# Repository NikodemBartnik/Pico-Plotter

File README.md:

# Pico Plotter

3D printed Raspberry Pi Pico H-Bot plotter programmed in MicroPython capable of drawing on paper and burning wood with versatip.

## Description

Main purpose of this project was to practice Python programing, design something cool and understand basics of how CNC machines, Gcode senders etc. works. This project is probably a great starting point to learn about basics of any CNC machine, as it is very simple and code is very minimal. 3D printed parts are optimized for support less printing (most of them but not all) and can be printed out of PLA. 
## Parts
#### Electronics
| Name                  | Amount | Link 1                                           | Link 2                                           | Link 3                                             |
| --------------------- | ------ | ------------------------------------------------ | ------------------------------------------------ | -------------------------------------------------- |
| Motors                | 2      | [https://bit.ly/3jrCJqY](https://bit.ly/3jrCJqY) | [https://bit.ly/3w9vsim](https://bit.ly/3w9vsim) | [https://amzn.to/3jlCU7o](https://amzn.to/3jlCU7o) |
| Stepper drivers       | 2      | [https://bit.ly/3608XSl](https://bit.ly/3608XSl) | [https://bit.ly/3Abaz9P](https://bit.ly/3Abaz9P) | [https://amzn.to/3yjyXV9](https://amzn.to/3yjyXV9) |
| Power supply          | 1      | [https://bit.ly/3qzeEjz](https://bit.ly/3qzeEjz) | [https://bit.ly/3qzJbxF](https://bit.ly/3qzJbxF) | [https://amzn.to/2T9NVOx](https://amzn.to/2T9NVOx) |
| Raspberry Pi Pico     | 1      | [https://bit.ly/2US6Spl](https://bit.ly/2US6Spl) | [https://bit.ly/3Aegafp](https://bit.ly/3Aegafp) | [https://amzn.to/2Tjz9Vd](https://amzn.to/2Tjz9Vd) |
| USB to UART converter | 1      | [https://bit.ly/3vZQIqF](https://bit.ly/3vZQIqF) | [https://bit.ly/36488Il](https://bit.ly/36488Il) | [https://amzn.to/3dsafcT](https://amzn.to/3dsafcT) |
| Micro servo           | 1      | [https://bit.ly/3A8MjoF](https://bit.ly/3A8MjoF) | [https://bit.ly/3jrOihS](https://bit.ly/3jrOihS) | [https://amzn.to/367zPQh](https://amzn.to/367zPQh) |
| Small components      | \-     |                                                  |                                                  |
#### Mechanics
| Name                         | Amount | Link 1                                           | Link 2                                           | Link 3                                             |
| ---------------------------- | ------ | ------------------------------------------------ | ------------------------------------------------ | -------------------------------------------------- |
| Aluminium profile 2020 600mm | 5      | [https://bit.ly/2UF2auT](https://bit.ly/2UF2auT) | [https://bit.ly/3hjPS2F](https://bit.ly/3hjPS2F) | [https://amzn.to/2UcRjs5](https://amzn.to/2UcRjs5) |
| MGN12 Linear rail 500mm      | 3      | [https://bit.ly/3qwWoHM](https://bit.ly/3qwWoHM) | [https://bit.ly/3jvdd4f](https://bit.ly/3jvdd4f) | [https://amzn.to/3Adcs5K](https://amzn.to/3Adcs5K) |
| MGN12H linear block          | 5      | [https://bit.ly/3qyKxsE](https://bit.ly/3qyKxsE) | [https://bit.ly/3AkVN0r](https://bit.ly/3AkVN0r) | [https://amzn.to/3h266yv](https://amzn.to/3h266yv) |
| GT2 Pulley                   | 2      | [https://bit.ly/3y7doGW](https://bit.ly/3y7doGW) | [https://bit.ly/3AbJDXp](https://bit.ly/3AbJDXp) | [https://amzn.to/3h2xc8I](https://amzn.to/3h2xc8I) |
| GT2 Belt                     | 5m     | [https://bit.ly/3h44CUH](https://bit.ly/3h44CUH) | [https://bit.ly/2U5sbDr](https://bit.ly/2U5sbDr) | [https://amzn.to/3x8Wgk0](https://amzn.to/3x8Wgk0) |
| 625ZZ Bearing                | 6      | [https://bit.ly/2USf3Sz](https://bit.ly/2USf3Sz) | [https://bit.ly/2TbLKKo](https://bit.ly/2TbLKKo) | [https://amzn.to/3vZVZyt](https://amzn.to/3vZVZyt) |
| Corner connectors            | 4      | [https://bit.ly/3h1PA1G](https://bit.ly/3h1PA1G) | [https://bit.ly/3qLDTj3](https://bit.ly/3qLDTj3) | [https://amzn.to/2Ua83Af](https://amzn.to/2Ua83Af) |
| Screws, T nuts etc.          |        |                                                  |                                                  |
#### Tools
| Name               | Link 1                                                         | Link 2                                                             | Link 3                                             |
| ------------------ | -------------------------------------------------------------- | ------------------------------------------------------------------ | -------------------------------------------------- |
| 3D printer         | [https://bit.ly/3qxoAu7](https://bit.ly/3qxoAu7)               | [https://bit.ly/3xZZaHU](https://bit.ly/3xZZaHU)                   | [https://amzn.to/3y25gHV](https://amzn.to/3y25gHV) |
| CNC Machine        | [https://indystry.cc/indymill/](https://indystry.cc/indymill/) | [https://indystry.cc/dremel-cnc/](https://indystry.cc/dremel-cnc/) |                                                    |
| Gas soldering iron | [https://amzn.to/3jEaGoH](https://amzn.to/3jEaGoH)             | [https://bit.ly/3dqgHBm](https://bit.ly/3dqgHBm)                   |
## Getting Started
You don't need any special libraries or additional files, assuming you have Python installed you have everything you need.
In order to upload script to Raspberry Pi Pico I used [Thonny](https://thonny.org/)

### Executing program
Before executing the Gcode sender change port of your raspberry pi pico and also path to the file that you want to print
To execute Gcode sender script simply change directory to where the file is located and type in the terminal:
```
python GcodeSender.py
```

## Help

If you need help, see the problem or want to contribute open an issue.

## Author
[Nikodem Bartnik](https://nikodembartnik.pl/)

## License

This project is licensed under the MIT license.

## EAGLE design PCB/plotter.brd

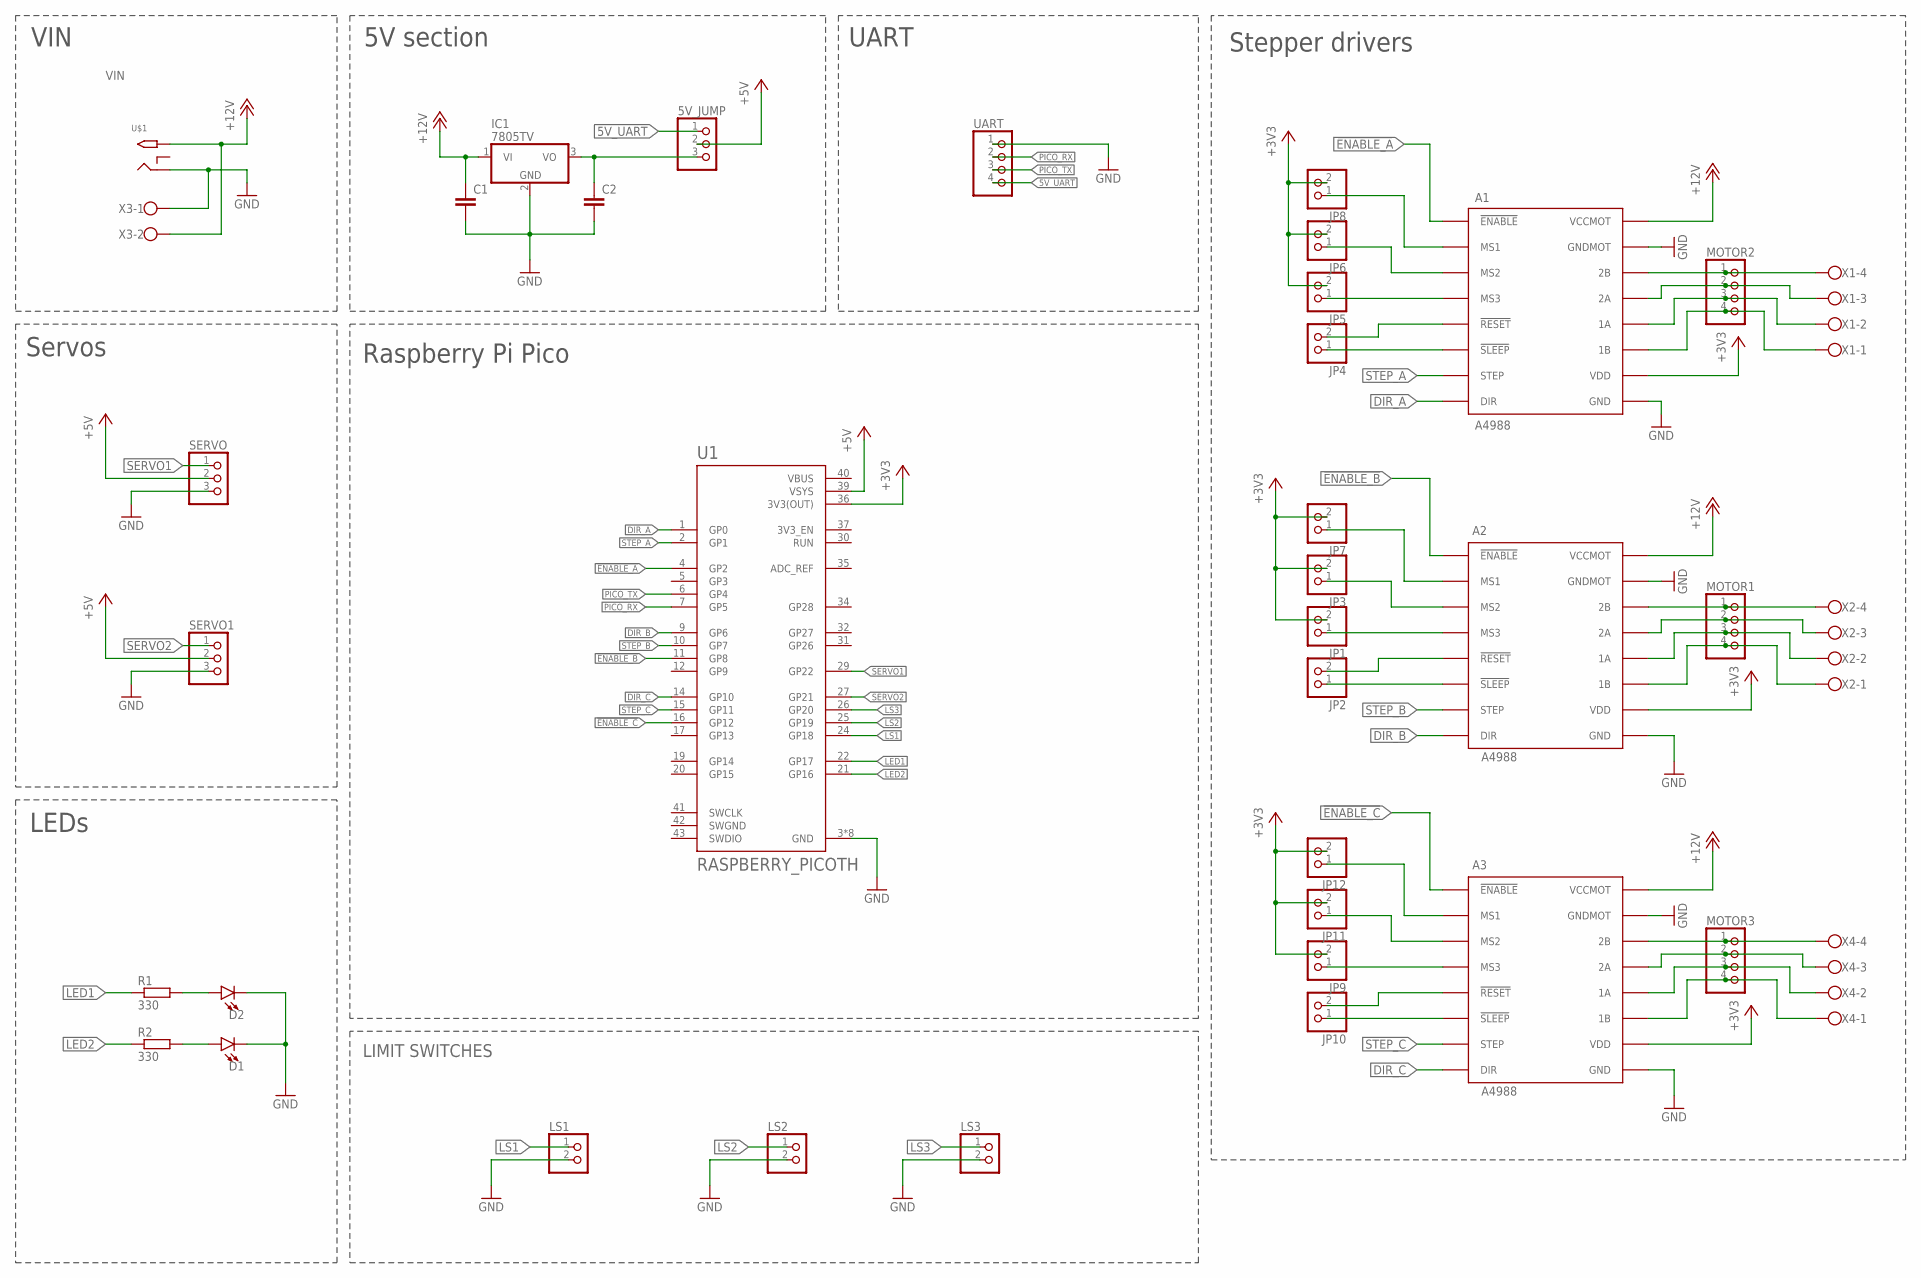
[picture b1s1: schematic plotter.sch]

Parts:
5V_JUMP: PINHD-1X3; 1X03
A1, A2, A3: A4988
C1, C2: C-EUC0805; C0805
D1, D2: LED5MM; LED_5MM
IC1: 7805TV; TO220V
JP1, JP2, JP3, JP4, JP5, JP6, JP7, JP8, JP9, JP10, JP11, JP12: PINHD-1X2; 1X02
LS1, LS2, LS3: PINHD-1X2; 1X02
MOTOR1, MOTOR2, MOTOR3: PINHD-1X4; 1X04
R1, R2: 330; R0805
SERVO, SERVO1: PINHD-1X3; 1X03
U1: RASPBERRY_PICOTH; PICO-PKG-TH
U$1: 2.1MMJACKTHM; PJ-102A
UART: PINHD-1X4; 1X04
X1, X2, X4: W237-4
X3: W237-102

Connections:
5V_UART: 5V_JUMP.1, UART.4
!ENABLE_A: A1.!ENABLE, U1.4 (GP2)
!ENABLE_B: A2.!ENABLE, U1.11 (GP8)
!ENABLE_C: A3.!ENABLE, U1.16 (GP12)
+3V3: A1.VDD, A2.VDD, A3.VDD, JP1.2, JP3.2, JP5.2, JP6.2, JP7.2, JP8.2, JP9.2, JP11.2, JP12.2, U1.36 (3V3(OUT))
+5V: 5V_JUMP.2, SERVO.2, SERVO1.2, U1.39 (VSYS)
+12V: A1.VCCMOT, A2.VCCMOT, A3.VCCMOT, C1.1, IC1.1 (VI), U$1.TIP, X3.2
DIR_A: A1.DIR, U1.1 (GP0)
DIR_B: A2.DIR, U1.9 (GP6)
DIR_C: A3.DIR, U1.14 (GP10)
GND: A1.GND, A1.GNDMOT, A2.GND, A2.GNDMOT, A3.GND, A3.GNDMOT, C1.2, C2.2, D1.K (C), D2.K (C), IC1.2 (GND), LS1.2, LS2.2, LS3.2, SERVO.3, SERVO1.3, U1.3 (GND), U1.8 (GND), U1.13 (GND), U1.18 (GND), U1.23 (GND), U1.28 (GND), U1.33 (GND), U1.38 (GND), U$1.RING, UART.1, X3.1
LED1: R1.1, U1.22 (GP17)
LED2: R2.1, U1.21 (GP16)
LS1: LS1.1, U1.24 (GP18)
LS2: LS2.1, U1.25 (GP19)
LS3: LS3.1, U1.26 (GP20)
unnamed: A1.2B, MOTOR2.1, X1.4
unnamed: A1.2A, MOTOR2.2, X1.3
unnamed: A1.1A, MOTOR2.3, X1.2
unnamed: A1.1B, MOTOR2.4, X1.1
unnamed: A2.2B, MOTOR1.1, X2.4
unnamed: A2.2A, MOTOR1.2, X2.3
unnamed: A2.1A, MOTOR1.3, X2.2
unnamed: A2.1B, MOTOR1.4, X2.1
unnamed: 5V_JUMP.3, C2.1, IC1.3 (VO)
unnamed: D2.A, R1.2
unnamed: D1.A, R2.2
unnamed: A2.!SLEEP, JP2.1
unnamed: A2.!RESET, JP2.2
unnamed: A2.MS3, JP1.1
unnamed: A2.MS2, JP3.1
unnamed: A2.MS1, JP7.1
unnamed: A1.!SLEEP, JP4.1
unnamed: A1.!RESET, JP4.2
unnamed: A1.MS3, JP5.1
unnamed: A1.MS2, JP6.1
unnamed: A1.MS1, JP8.1
unnamed: A3.2B, MOTOR3.1, X4.4
unnamed: A3.2A, MOTOR3.2, X4.3
unnamed: A3.1A, MOTOR3.3, X4.2
unnamed: A3.1B, MOTOR3.4, X4.1
unnamed: A3.!SLEEP, JP10.1
unnamed: A3.!RESET, JP10.2
unnamed: A3.MS3, JP9.1
unnamed: A3.MS2, JP11.1
unnamed: A3.MS1, JP12.1
PICO_RX: U1.7 (GP5), UART.2
PICO_TX: U1.6 (GP4), UART.3
SERVO1: SERVO.1, U1.29 (GP22)
SERVO2: SERVO1.1, U1.27 (GP21)
STEP_A: A1.STEP, U1.2 (GP1)
STEP_B: A2.STEP, U1.10 (GP7)
STEP_C: A3.STEP, U1.15 (GP11)
SWGND: U1.42 (SWGND)
VBUS: U1.40 (VBUS)

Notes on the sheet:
VIN
LIMIT SWITCHES
LEDs
Servos
5V section
UART
Stepper drivers
Raspberry Pi Pico

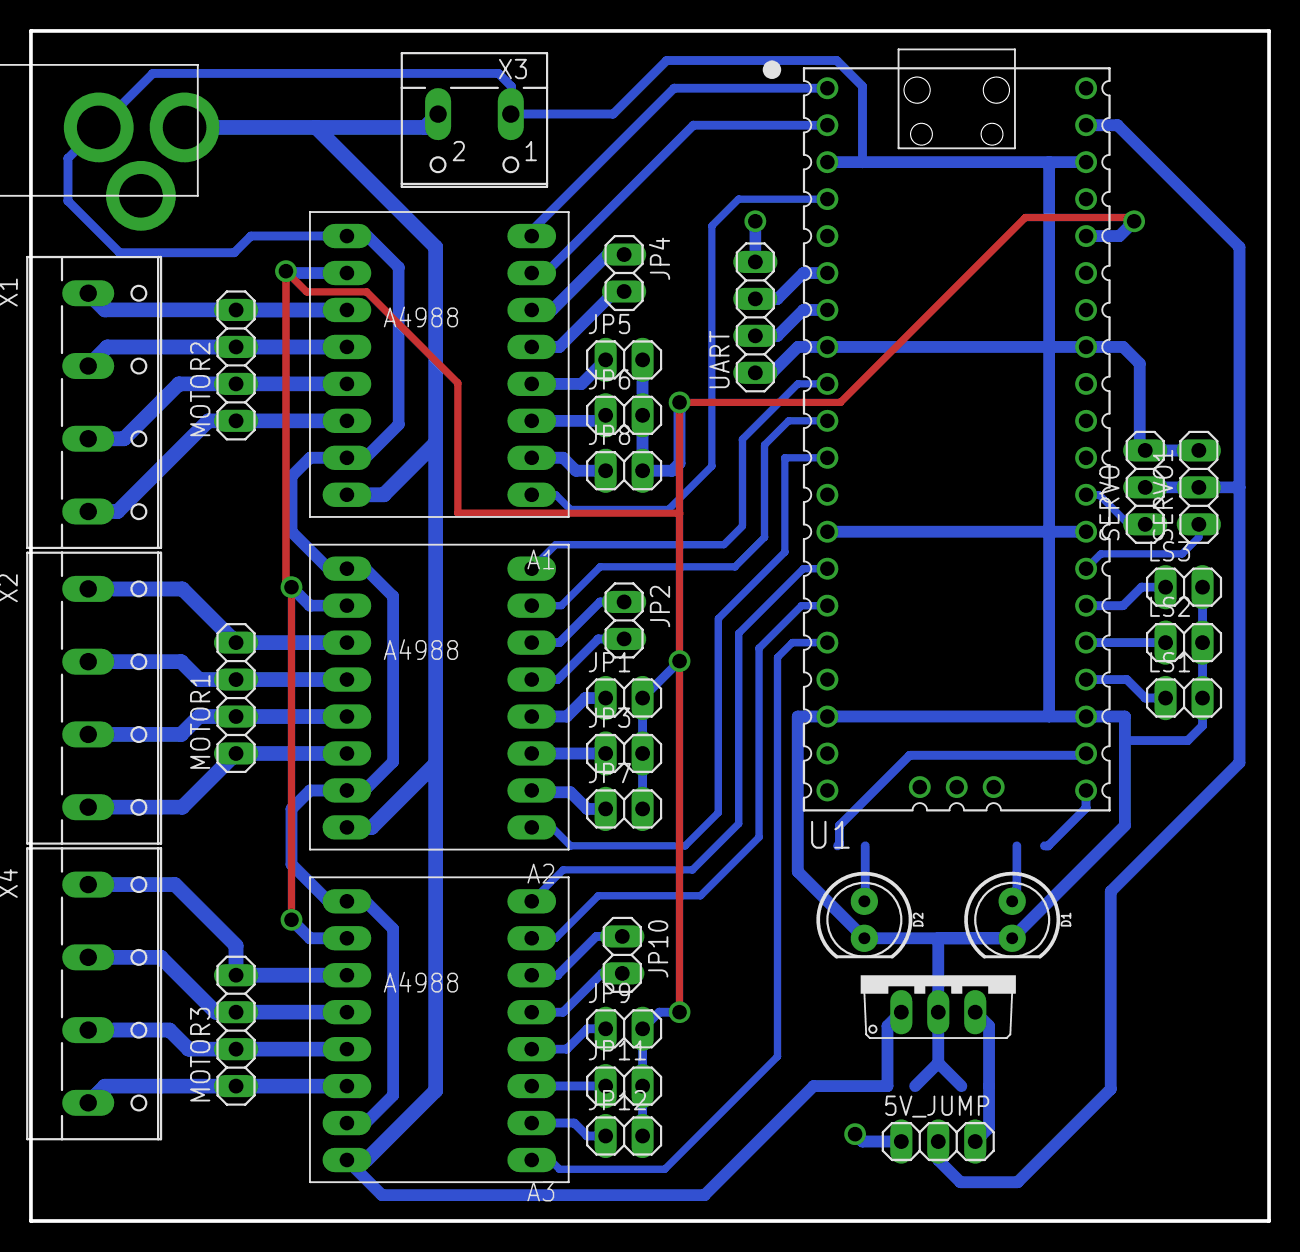
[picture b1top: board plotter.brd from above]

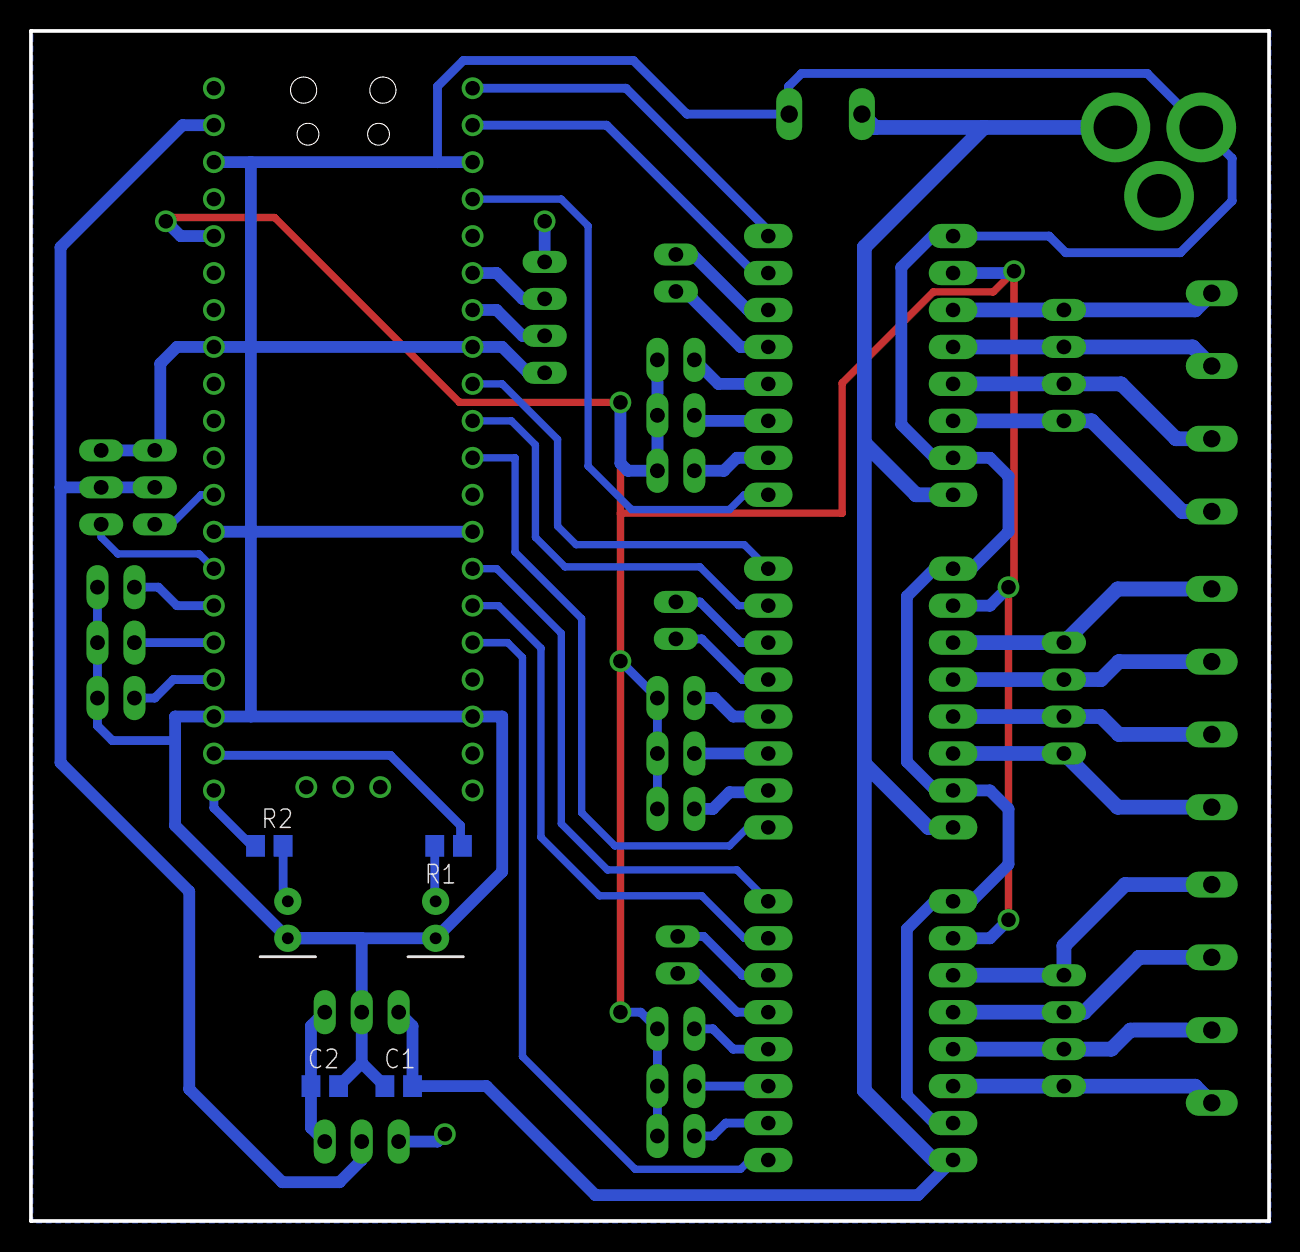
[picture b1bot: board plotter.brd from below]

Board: 2 copper layers, 85.1 x 81.8 mm, 38 parts (4 on the bottom side), 53 nets.

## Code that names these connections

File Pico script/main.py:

import utime
from machine import Pin, UART, PWM
uart = machine.UART(1, 115200)

#constants
STEPSPERMM = 80
MMPERSTEP = 1/STEPSPERMM
DIR_A = 0
STEP_A = 1
nENABLE_A = 2
STEP_DELAY = 20

DIR_B = 6
STEP_B = 7
nENABLE_B = 8

DIR_C = 10
STEP_C = 11
nENABLE_C = 12

SERVO_PIN = 21

x_step_pos = 0
y_step_pos = 0


dir_A = Pin(DIR_A, Pin.OUT)
step_A = Pin(STEP_A, Pin.OUT)
nenable_A = Pin(nENABLE_A, Pin. OUT)

dir_B = Pin(DIR_B, Pin.OUT)
step_B = Pin(STEP_B, Pin.OUT)
nenable_B = Pin(nENABLE_B, Pin. OUT)

servo = None

def EnableMotors():
    nenable_A.value(0)
    nenable_B.value(0)
    

def DisableMotors():
    nenable_A.value(1)
    nenable_B.value(1)
    

#a = 0 move A, a = 1 move B
def OneStep(a, direction):
    if a == 0:
        dir_A.value(direction)
        step_A.value(0)
        step_A.value(1)
    elif a == 1:
        dir_B.value(direction)
        step_B.value(0)
        step_B.value(1)
        
    

#To move to (X, Y) we need to calculate dA = dX + dY and dB = dX - dY
def MoveToPosition(x, y):
    global x_step_pos
    global y_step_pos
    #x and y steps to do, different than a and b steps to do
    x = x/MMPERSTEP
    y = y/MMPERSTEP
    x_steps_to_do = round(x) - x_step_pos
    y_steps_to_do = round(y) - y_step_pos
    a_steps_to_do = x_steps_to_do + y_steps_to_do
    b_steps_to_do = x_steps_to_do - y_steps_to_do
    x_step_pos = x
    y_step_pos = y
    
    #deciding on which way the motors should spin
    directionA = 0 if a_steps_to_do > 0 else 1
    directionB = 0 if b_steps_to_do > 0 else 1
    
    #after obatining the direction we can convert to absolute values for simplicity
    a_steps_to_do = abs(a_steps_to_do)
    b_steps_to_do = abs(b_steps_to_do)

    #here we will store the error for the axis with sliced movement
    if a_steps_to_do == b_steps_to_do:
        for i in range(a_steps_to_do):
            OneStep(0, directionA)
            OneStep(1, directionB)
            StepsDelay()
        
    else:
        sliced_axis_error = 0
        sliced_axis_increment = b_steps_to_do/a_steps_to_do if a_steps_to_do > b_steps_to_do else a_steps_to_do/b_steps_to_do
        
        if a_steps_to_do > b_steps_to_do:
            for i in range(a_steps_to_do):
                OneStep(0, directionA)
                sliced_axis_error += sliced_axis_increment
                if sliced_axis_error >= 1:
                    OneStep(1, directionB)
                    sliced_axis_error -= 1
                StepsDelay()
            
        elif a_steps_to_do < b_steps_to_do:
            for i in range(b_steps_to_do):
                OneStep(1, directionB)
                sliced_axis_error += sliced_axis_increment
                if sliced_axis_error >= 1:
                    OneStep(0, directionA)
                    sliced_axis_error -= 1
                StepsDelay()
    
    
    
def StepsDelay():
    utime.sleep_us(STEP_DELAY)
    
    
def UartRead():
    return uart.readline()


def UartSendOK():
    uart.write('OK\n')
    

def ProcessGcode(inputLine):
    UartSendOK()
    #dictionary with variables to return
    toReturn = {}
    inputLine = inputLine.strip('\n\r')
    inputLine = inputLine.split(';', 1)[0]
    print(inputLine)
    if len(inputLine) > 0:
        gcode = inputLine.split(' ')
        for command in gcode:
            if command[0] == 'X':
                #do things with X
                toReturn['X'] = command[1:]
            elif command[0] == 'Y':
                #do things with Y
                toReturn['Y'] = command[1:]
            elif command[0] == 'Z':
                #do things with Z
                toReturn['Z'] = command[1:]
            elif command[0] == 'F':
                #do things with F
                toReturn['F'] = command[1:]
            elif command[0] == 'G':
                #do things with G
                toReturn['G'] = command[1:]
    return toReturn


def ExecuteGcode(commands):
    global x_step_pos
    global y_step_pos
    global STEP_DELAY
    if 'F' in commands:        
        STEP_DELAY = int(5000 - 5*int(commands['F']))
        if STEP_DELAY < 20: STEP_DELAY = 20
        print("New step delay: " + str(STEP_DELAY))
    if 'Z' in commands:
        ServoWrite(0 if float(commands['Z']) > 0.1 else 30)
    if 'X' in commands or 'Y' in commands:
        MoveToPosition(float(commands['X']) if 'X' in commands else x_step_pos*MMPERSTEP, float(commands['Y']) if 'Y' in commands else y_step_pos*MMPERSTEP)
    if 'G' in commands:
        if(commands['G'] == '28'):
            x_step_pos = 0
            y_step_pos = 0
    
                
def ServoWrite(angle):
    servo.duty_ns(int((angle/180)*1000000+700000))
    utime.sleep_ms(100)


def ServoInit():
    global servo
    servo = PWM(Pin(21))
    servo.freq(50)
    servo.duty_ns(700000)
    
    
EnableMotors()
ServoInit()
while(1):
    ExecuteGcode(ProcessGcode(str(UartRead(), "utf-8")))

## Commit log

2021-06-28 Added readme to scripts
2021-06-28 Added Gcode sender script and MicroPython code for Raspberry Pi Pico
2021-06-29 Code cleanup
2021-06-29 Updated readme and parts list
2021-06-29 Readme fix
2021-06-29 Added parts list to readme
2021-06-30 Updated readme tables

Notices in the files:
parts and their libraries:
SparkFun-LED: Licensing: Creative Commons ShareAlike 4.0 International - https://creativecommons.org/licenses/by-sa/4.0
